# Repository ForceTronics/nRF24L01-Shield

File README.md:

# nRF24L01-Shield
This repository holds the Eagle files for an open source nRF24L01 Shield for Arduino. This Shield was designed by ForceTronics LLC and can be purchased at forcetronics.com

Note the Eagle Project nRF24L01 Shield uses parts from the ForceTronics.lbr file so you need to add it to your "lbr" folder.

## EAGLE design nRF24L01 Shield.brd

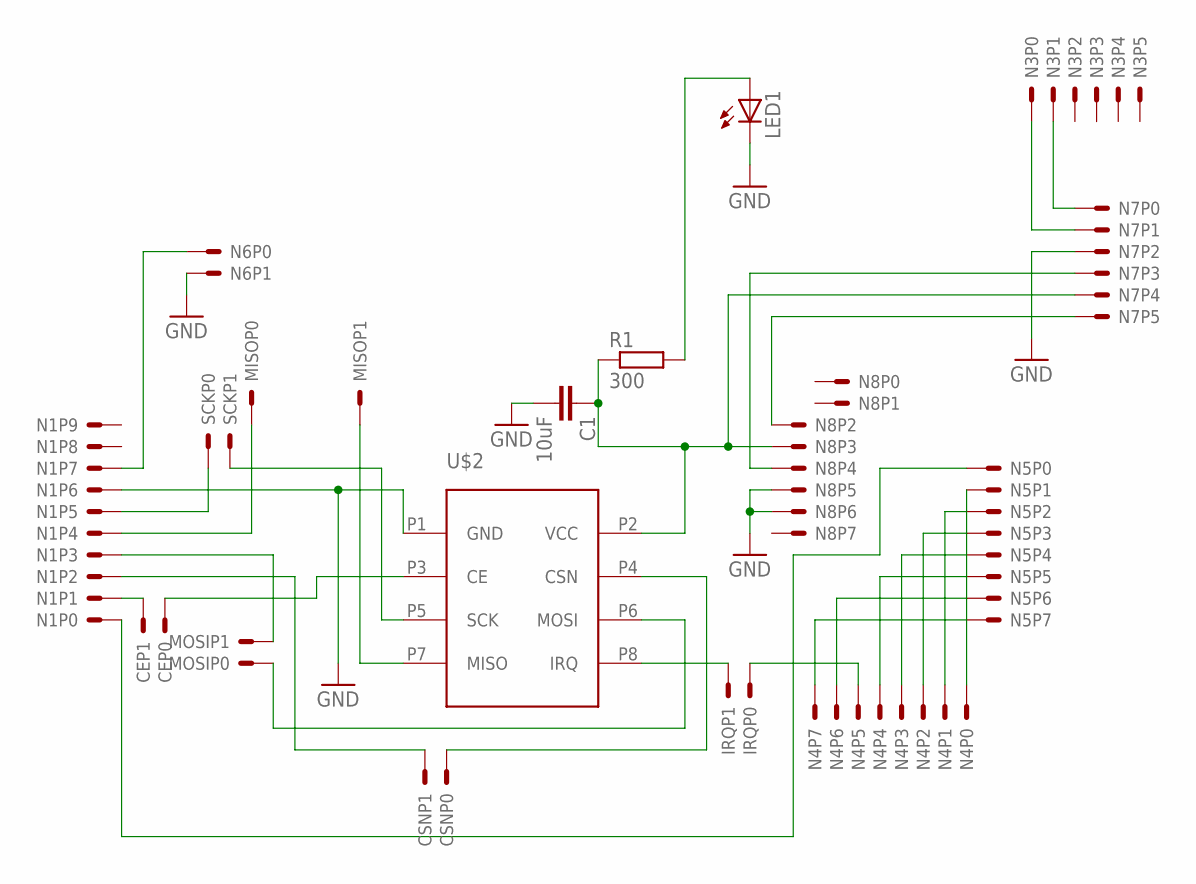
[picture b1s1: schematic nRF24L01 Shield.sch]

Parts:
C1: 10uF; C2.5-4
CE: 2PINHEADER
CSN: 2PINHEADER
IRQ: 2PINHEADER
LED1: LED3MM
MISO: 2PINHEADER
MOSI: 2PINHEADER
N1: 10PINHEADER
N3, N7: 6PINHEADER
N4, N5, N8: 8PINHEADER
N6: 2PINHEADER
R1: 300; 0207/10
SCK: 2PINHEADER
U$2: NRF24L01A; NRF24L01

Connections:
GND: C1.2, LED1.K (C), N1.P6, N6.P1, N7.P2, N8.P5, N8.P6, U$2.P1 (GND)
unnamed: CE.P0, U$2.P3 (CE)
unnamed: CSN.P0, U$2.P4 (CSN)
unnamed: MOSI.P0, U$2.P6 (MOSI)
unnamed: MISO.P1, U$2.P7 (MISO)
unnamed: SCK.P1, U$2.P5 (SCK)
unnamed: C1.1, N7.P4, N8.P3, R1.1, U$2.P2 (VCC)
unnamed: N1.P5, SCK.P0
unnamed: IRQ.P0, N4.P5
unnamed: LED1.A, R1.2
unnamed: MISO.P0, N1.P4
unnamed: MOSI.P1, N1.P3
unnamed: CSN.P1, N1.P2
unnamed: CE.P1, N1.P1
unnamed: IRQ.P1, U$2.P8 (IRQ)
unnamed: N4.P7, N5.P7
unnamed: N4.P6, N5.P6
unnamed: N4.P4, N5.P5
unnamed: N4.P3, N5.P4
unnamed: N4.P2, N5.P3
unnamed: N4.P1, N5.P2
unnamed: N4.P0, N5.P1
unnamed: N1.P0, N5.P0
unnamed: N1.P7, N6.P0
unnamed: N7.P5, N8.P2
unnamed: N3.P0, N7.P1
unnamed: N3.P1, N7.P0
unnamed: N7.P3, N8.P4

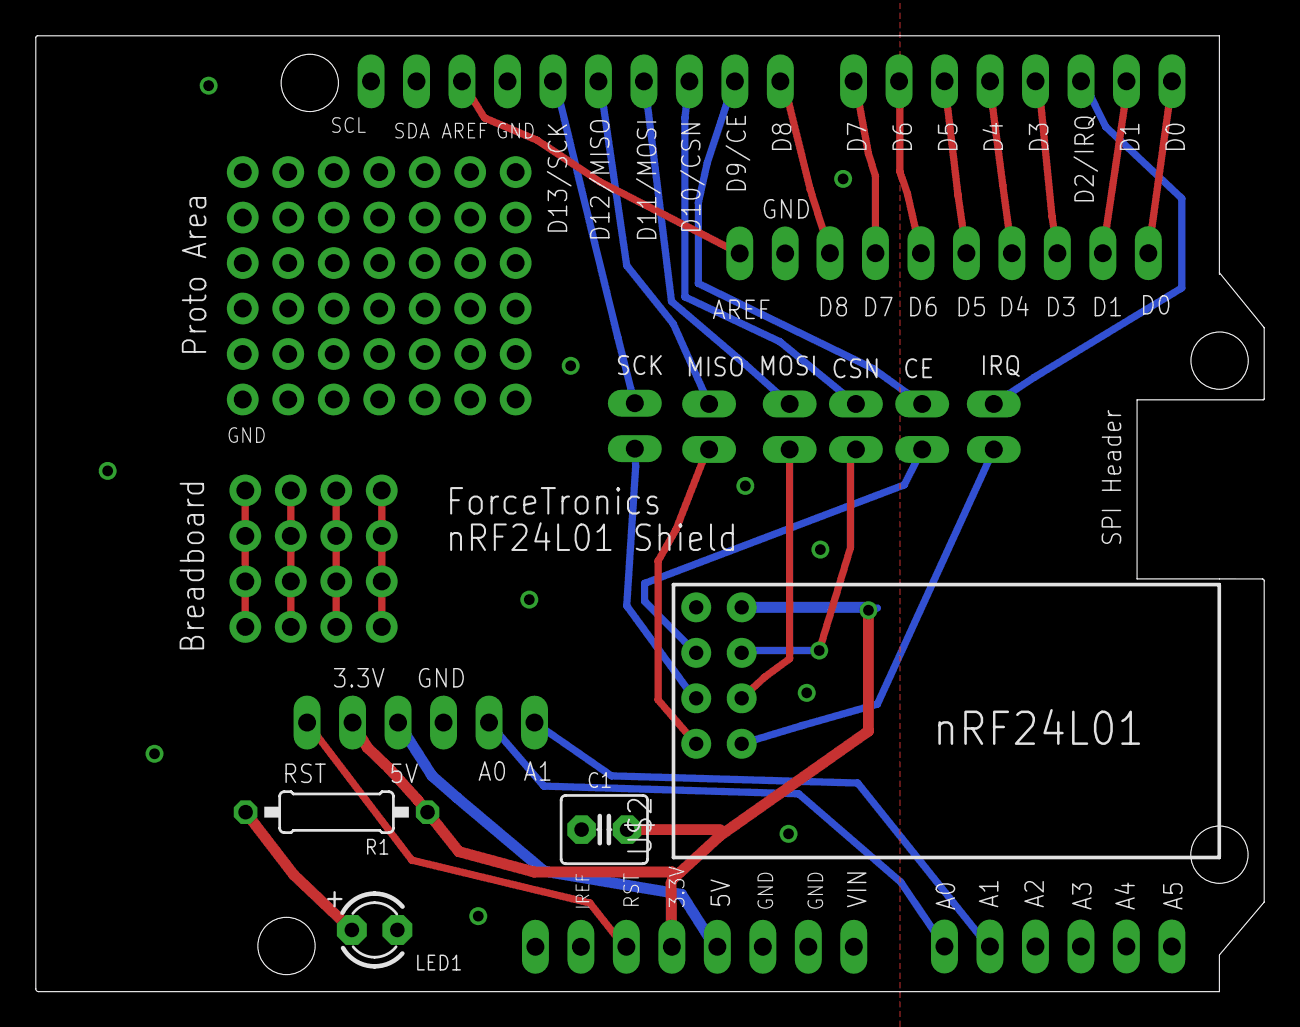
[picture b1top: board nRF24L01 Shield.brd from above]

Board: 2 copper layers, 68.6 x 53.4 mm, 17 parts (0 on the bottom side), 28 nets.
